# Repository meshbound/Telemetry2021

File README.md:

# Telemetry 2021 Madison West Rocket Club

This is the repository for the 2021 MWR SLI Telemetry Software

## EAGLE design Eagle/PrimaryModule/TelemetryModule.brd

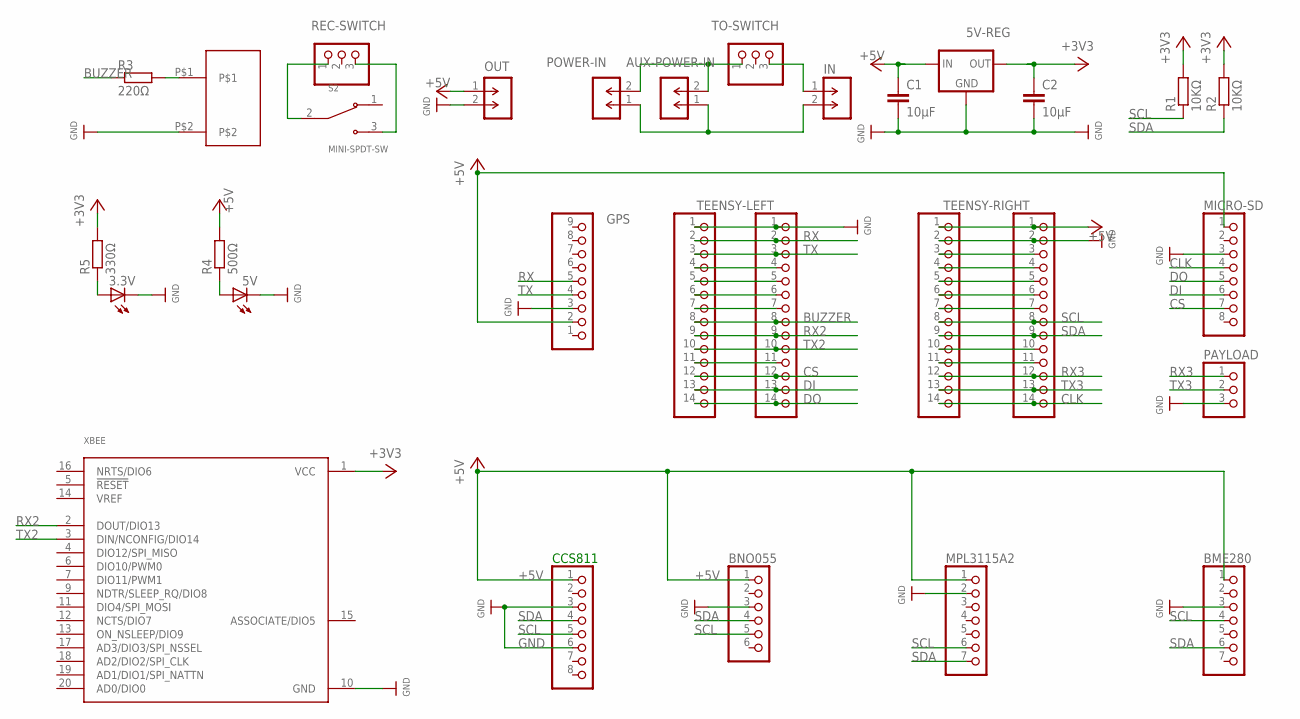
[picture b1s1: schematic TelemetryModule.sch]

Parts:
3.3V, 5V: LED5MM
5V-REG: LD1117V33
AUX-POWER-IN: M-1X02-SIP-100-40Y; SIP-100-02-40Y
BME280: HEADER-1X770MIL; 1X07_ROUND_70
BNO055: HEADER-1X676MIL; 1X06_ROUND_76
C1, C2: 10µF; C2.5-3
CCS811: HEADER-1X870MIL; 1X08_ROUND_70
GPS: HEADER-1X970MIL; 1X09_ROUND_70
IN: M-1X02-SIP-100-40Y; SIP-100-02-40Y
MICRO-SD: PINHD-1X8BIG; 1X08-BIG
MPL3115A2: HEADER-1X770MIL; 1X07_ROUND_70
OUT: M-1X02-SIP-100-40Y; SIP-100-02-40Y
PAYLOAD: PINHD-1X3CB; 1X03-CLEANBIG
POWER-IN: M-1X02-SIP-100-40Y; SIP-100-02-40Y
R1, R2: 10KΩ; 0207/10
R3: 220Ω; 0207/10
R4: 500Ω; 0207/10
R5: 330Ω; 0207/10
REC-SWITCH: PINHD-1X3CB; 1X03-CLEANBIG
S2: MINI-SPDT-SW; SW_MINI-SPDT-SW
TEENSY-LEFT: PINHD-1X14-CB; 1X14-CB
TEENSY-LEFT-DUPE: PINHD-1X14-CB; 1X14-CB
TEENSY-RIGHT: PINHD-1X14-CB; 1X14-CB
TEENSY-RIGHT-DUPE: PINHD-1X14-CB; 1X14-CB
TO-SWITCH: PINHD-1X3CB; 1X03-CLEANBIG
U$3: PS1240P02BT
XBEE: XBP9B-XCST-002; DIP2200W51P200L3294H279Q20P

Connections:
+3V3: 5V-REG.OUT, C2.1, R1.2, R2.2, R5.2, XBEE.1 (VCC)
+5V: 5V-REG.IN, BME280.1, BNO055.1, C1.1, CCS811.1, GPS.2, MICRO-SD.1, MPL3115A2.1, OUT.1, R4.2, TEENSY-RIGHT.1, TEENSY-RIGHT-DUPE.1
BUZZER: R3.1, TEENSY-LEFT.8, TEENSY-LEFT-DUPE.8
CLK: MICRO-SD.4, TEENSY-RIGHT.14, TEENSY-RIGHT-DUPE.14
CS: MICRO-SD.7, TEENSY-LEFT.12, TEENSY-LEFT-DUPE.12
DI: MICRO-SD.6, TEENSY-LEFT.13, TEENSY-LEFT-DUPE.13
DO: MICRO-SD.5, TEENSY-LEFT.14, TEENSY-LEFT-DUPE.14
GND: 3.3V.K (C), 5V.K (C), 5V-REG.GND, BME280.3, BNO055.3, C1.2, C2.2, CCS811.3, CCS811.6, GPS.3, MICRO-SD.3, MPL3115A2.2, OUT.2, PAYLOAD.3, TEENSY-LEFT.1, TEENSY-LEFT-DUPE.1, TEENSY-RIGHT.2, TEENSY-RIGHT-DUPE.2, U$3.P$2, XBEE.10 (GND)
unnamed: AUX-POWER-IN.1, IN.2, POWER-IN.1
unnamed: AUX-POWER-IN.2, POWER-IN.2, TO-SWITCH.1
unnamed: REC-SWITCH.1, S2.2
unnamed: REC-SWITCH.3, S2.3
unnamed: IN.1, TO-SWITCH.3
unnamed: R3.2, U$3.P$1
unnamed: TEENSY-LEFT.4, TEENSY-LEFT-DUPE.4
unnamed: TEENSY-LEFT.5, TEENSY-LEFT-DUPE.5
unnamed: TEENSY-LEFT.6, TEENSY-LEFT-DUPE.6
unnamed: TEENSY-LEFT.7, TEENSY-LEFT-DUPE.7
unnamed: TEENSY-LEFT.11, TEENSY-LEFT-DUPE.11
unnamed: TEENSY-RIGHT.7, TEENSY-RIGHT-DUPE.7
unnamed: TEENSY-RIGHT.6, TEENSY-RIGHT-DUPE.6
unnamed: TEENSY-RIGHT.5, TEENSY-RIGHT-DUPE.5
unnamed: TEENSY-RIGHT.4, TEENSY-RIGHT-DUPE.4
unnamed: TEENSY-RIGHT.3, TEENSY-RIGHT-DUPE.3
unnamed: 5V.A, R4.1
unnamed: TEENSY-RIGHT.10, TEENSY-RIGHT-DUPE.10
unnamed: TEENSY-RIGHT.11, TEENSY-RIGHT-DUPE.11
unnamed: 3.3V.A, R5.1
RX: GPS.5, TEENSY-LEFT.2, TEENSY-LEFT-DUPE.2
RX2: TEENSY-LEFT.9, TEENSY-LEFT-DUPE.9, XBEE.2 (DOUT/DIO13)
RX3: PAYLOAD.1, TEENSY-RIGHT.12, TEENSY-RIGHT-DUPE.12
SCL: BME280.4, BNO055.5, CCS811.5, MPL3115A2.6, R1.1, TEENSY-RIGHT.8, TEENSY-RIGHT-DUPE.8
SDA: BME280.6, BNO055.4, CCS811.4, MPL3115A2.7, R2.1, TEENSY-RIGHT.9, TEENSY-RIGHT-DUPE.9
TX: GPS.4, TEENSY-LEFT.3, TEENSY-LEFT-DUPE.3
TX2: TEENSY-LEFT.10, TEENSY-LEFT-DUPE.10, XBEE.3 (DIN/NCONFIG/DIO14)
TX3: PAYLOAD.2, TEENSY-RIGHT.13, TEENSY-RIGHT-DUPE.13

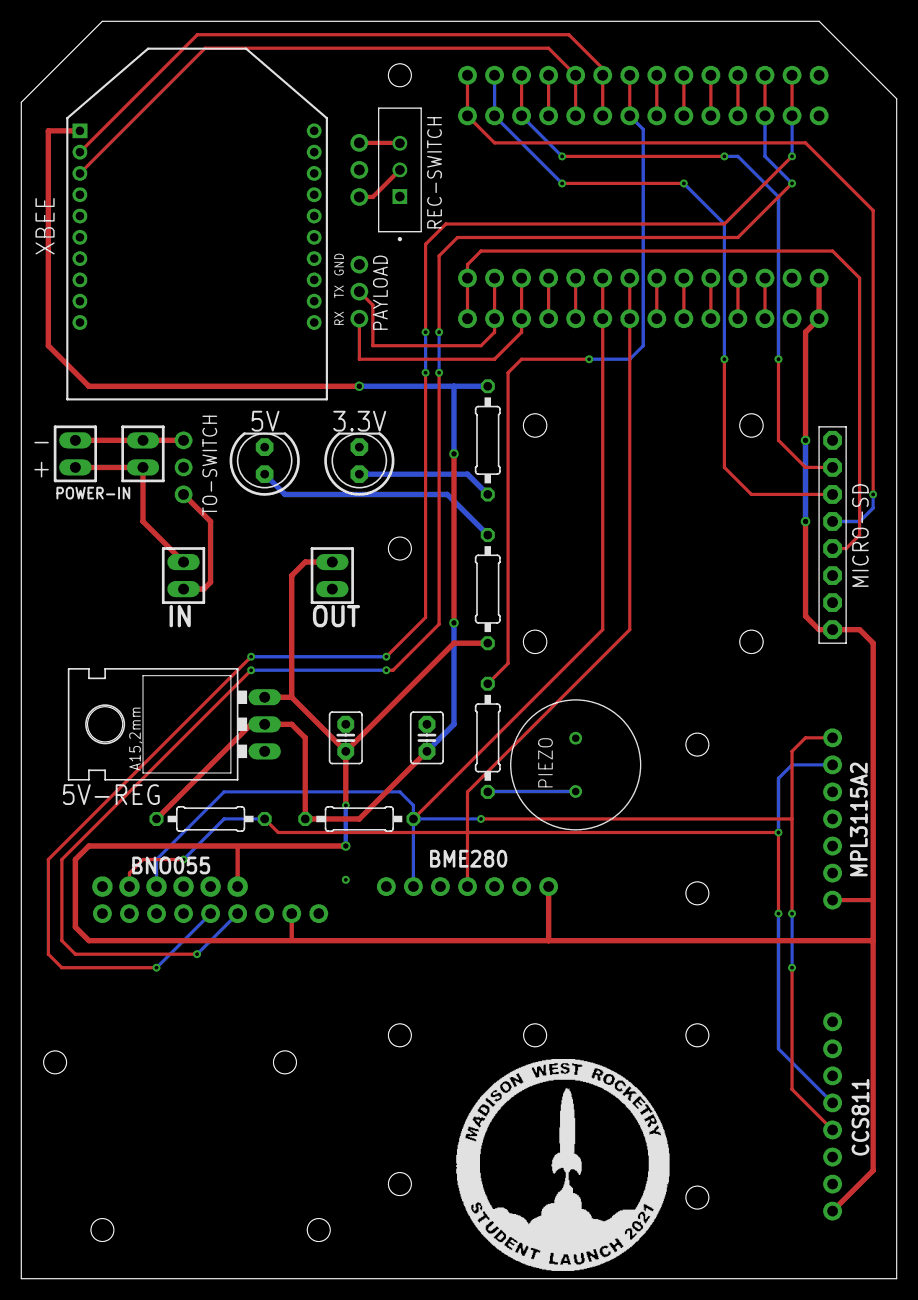
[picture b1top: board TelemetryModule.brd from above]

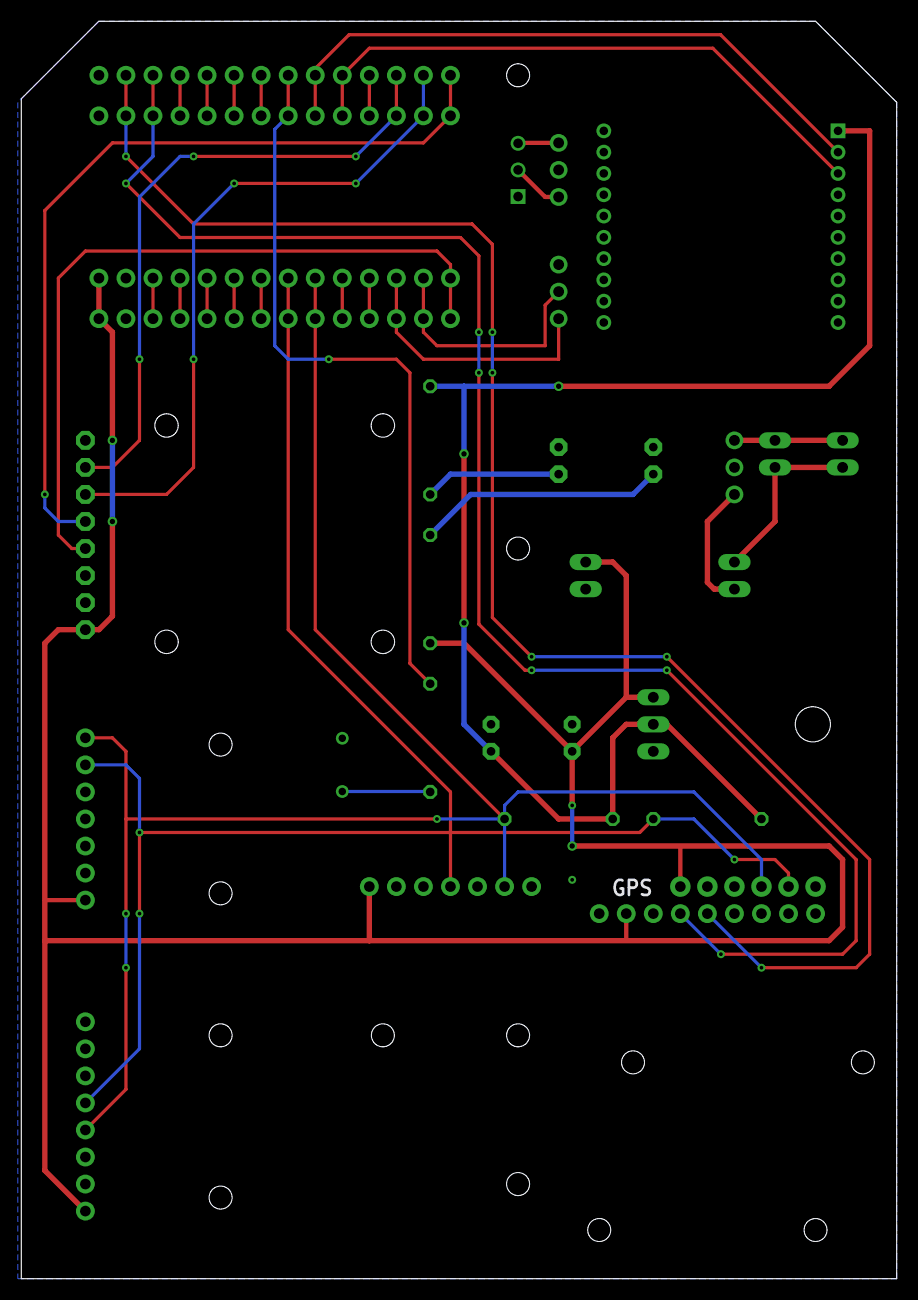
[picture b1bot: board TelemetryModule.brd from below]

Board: 2 copper layers, 82.2 x 118.1 mm, 30 parts (2 on the bottom side), 36 nets.

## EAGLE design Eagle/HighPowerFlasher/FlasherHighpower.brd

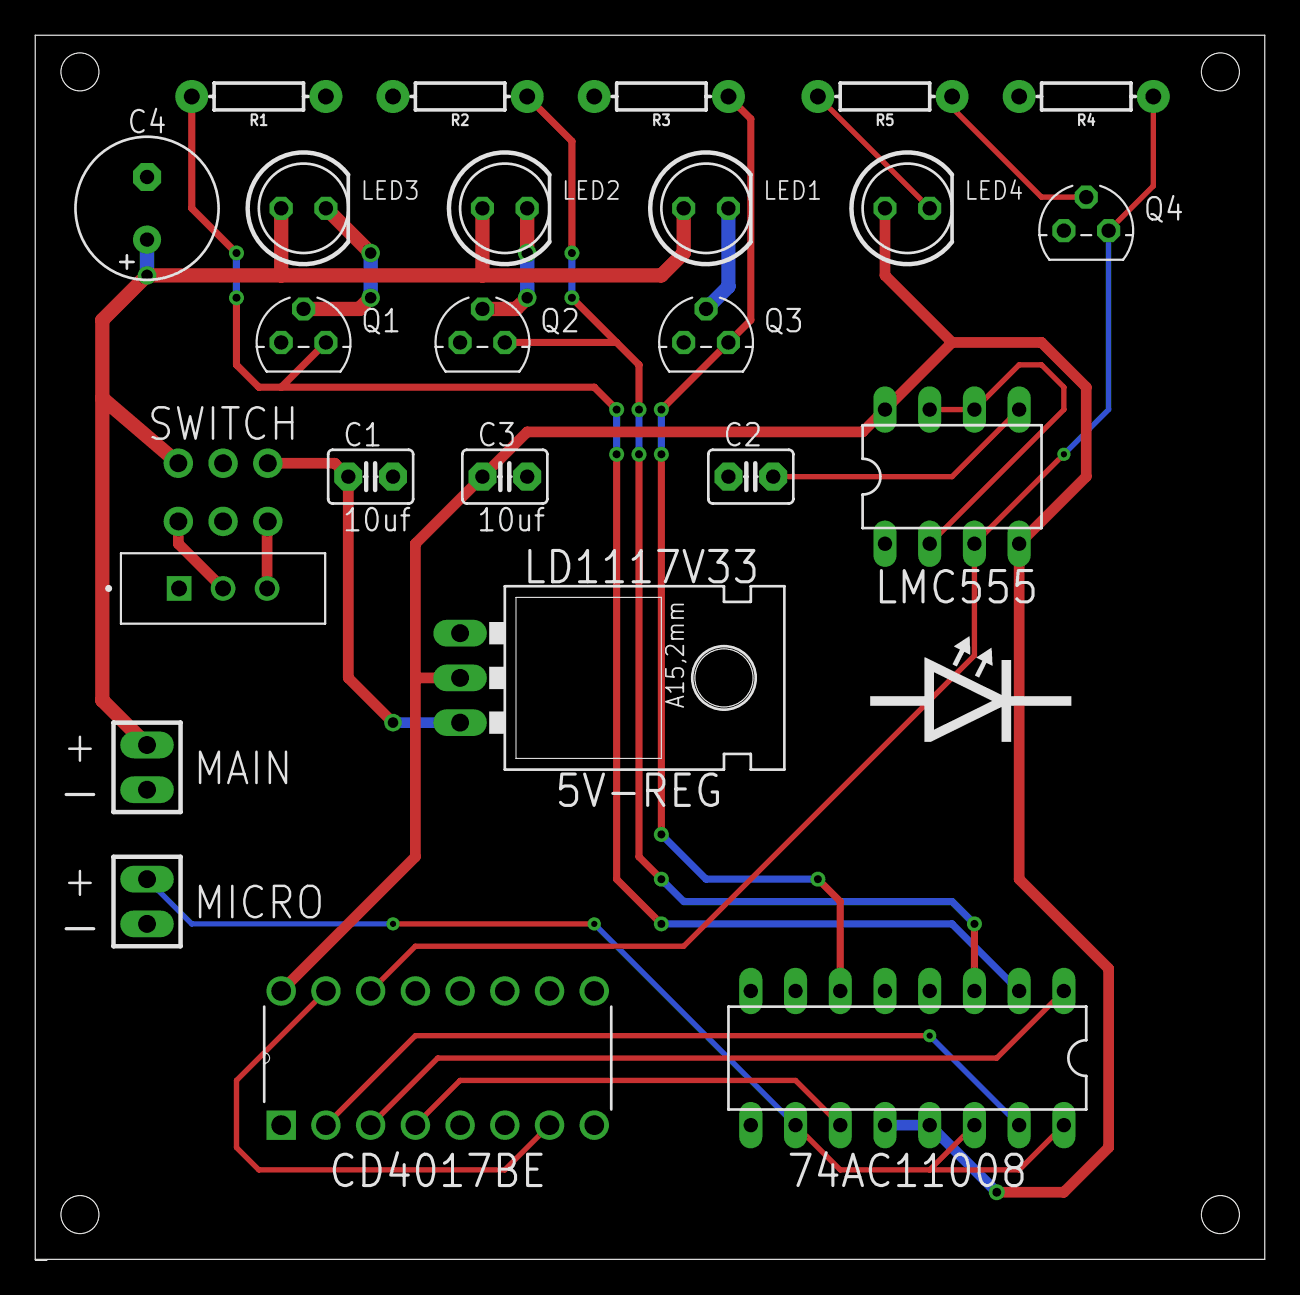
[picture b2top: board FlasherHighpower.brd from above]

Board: 2 copper layers, 69.8 x 69.5 mm, 26 parts (0 on the bottom side), 22 nets.

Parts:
5V-REG: LD1117V33
C1, C2, C3: 10uf; C2.5-3
C4: E3,5-8
IC1: 74AC11008; DIL16
LED1, LED2, LED3, LED4: LED5MM
MICRO-ENABLE: M-1X02-SIP-100-40Y; SIP-100-02-40Y
POWER-IN: M-1X02-SIP-100-40Y; SIP-100-02-40Y
Q1, Q2, Q3, Q4: BSS296; TO92
R1, R2, R3, R4, R5: 1K; AXIAL-0.3
REC-SWITCH: 1X03-CLEANBIG
S1: MINI-SPDT-SW; SW_MINI-SPDT-SW
TO-SWITCH: 1X03-CLEANBIG
U2: CD4017BE; DIP254P762X508-16
U$2: LMC555; 8-DIP

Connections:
5V: 5V-REG.OUT, C3.1, IC1.12, IC1.13, LED4.A, U2.16, U$2.4, U$2.8
12V: C4.+, LED1.A, LED2.A, LED3.A, POWER-IN.2, TO-SWITCH.1
+5V: 5V-REG.IN, C1.1, TO-SWITCH.3
GND: 5V-REG.GND, C1.2, C2.2, C3.2, C4.-, IC1.4, IC1.5, MICRO-ENABLE.1, POWER-IN.1, Q1.3, Q2.3, Q3.3, Q4.3, R1.P$2, R2.P$2, R3.P$2, R4.P$2, U2.8, U2.13, U$2.1
MICRO_ENABLE: IC1.10, IC1.14, IC1.16, MICRO-ENABLE.2
unnamed: LED1.K, Q3.2
unnamed: LED2.K, Q2.2
unnamed: Q4.1, R4.P$1, U2.14, U$2.3
unnamed: LED3.K, Q1.2
unnamed: REC-SWITCH.3, S1.3
unnamed: REC-SWITCH.1, S1.2
unnamed: C2.1, U$2.5
unnamed: Q4.2, R5.P$1
unnamed: LED4.K, R5.P$2
Q0: IC1.2, Q1.1, R1.P$1
Q0I: IC1.1, U2.3
Q1: IC1.3, Q2.1, R2.P$1
Q1I: IC1.15, U2.2
Q2: IC1.6, Q3.1, R3.P$1
Q2I: IC1.11, U2.4
RST: U2.7, U2.15
TTD: U$2.2, U$2.6, U$2.7

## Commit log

2020-02-06 Create TelemetryModule.ino
    Create the telemetry module main file
2020-02-06 Update TelemetryModule.ino
    Cleaned up imports and variables
2020-02-06 Added serial python files
    Added base communication files
2020-02-06 Update TelemetryModule.ino
    Reformatted time methods
2020-02-06 Update TelemetryModule.ino
    Fixed up sensor methods
2020-02-06 Update TelemetryModule.ino
    Major cleanup and formatting
2020-02-15 Added primary files
    Added files for data site
2020-02-15 Ground UI
    Added primary files for processing data and UI
2020-02-17 Inital edits to recieving end
    Small changes to the recieving end
2020-02-17 Implemented new data reception
    Removed multi CSV method
    added JSON file temp for front end to grab and dump file for later reading
2020-02-18 Progress on the backend
    Fully implemented the data dump and current data json
2020-02-19 Backend progress
    removed uneeded code
2020-02-22 Backend progress
    Nearly fully functional
    data is now properly requested
2020-02-22 Frontend progress
    Implemented severial sensors
2020-02-22 Cleaning up
    Removed redudant files
    shorted call on data
2020-02-26 Improved JSON
    Made more clear JSON dicts, also added a method for controlling the formating and applying large datasets to the JSON.
2020-02-29 Added templates
    Added the base program for the turret and the base file for producing test data.
2020-03-01 Sensor fixes
    Added support for BME 280, progress on implementation of rate of transfer
2020-03-01 Minor changes
    Folder structure
    Updates to JSON
    Progress on a ground receiving program
2020-03-06 Logging changes
    added new python file to read log files and partially implemented the average method
2020-03-07 Bug fixes
    Minor bug fixes
2020-03-11 Formatting & GPS
    progress on GPS init
2021-01-23 Major updates
    Added python visualization
    Refactored code for recieving end
    Cleaned up on-board code
2021-02-05 Fixed up payload end
    Cleaned up code
    Added payload print option (Serial3)
    Made sure that booleans are used properly for when to send/request data
2021-02-10 Minor fixes
    Trying to get UART to work with a PI again
2021-02-25 Payload files
    Added payload debugging program
2021-02-25 Updating file structure
    Reorganized files
    Added example code for payload
2021-02-25 Adjusted file structure
2021-02-25 Removed random test
2021-02-25 Removed broken threadkill
2021-03-11 Added PCBs and minor fixes
    Added PCB files
    And minor fixes for the python files
2021-03-13 Finished code for detecting a launch
    Implemented detection of a launch in a class (Listener) adding onto code to receive serial data from the telemetry module and payload altimeter
2021-03-14 Added flight report builder
2021-03-18 trolololololo
2024-08-04 Archive cleanup

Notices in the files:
parts and their libraries:
SparkFun-Resistors: Licensing: Creative Commons ShareAlike 4.0 International - https://creativecommons.org/licenses/by-sa/4.0
con-headers-jp: Copyright (C) 2008, Bob Starr
